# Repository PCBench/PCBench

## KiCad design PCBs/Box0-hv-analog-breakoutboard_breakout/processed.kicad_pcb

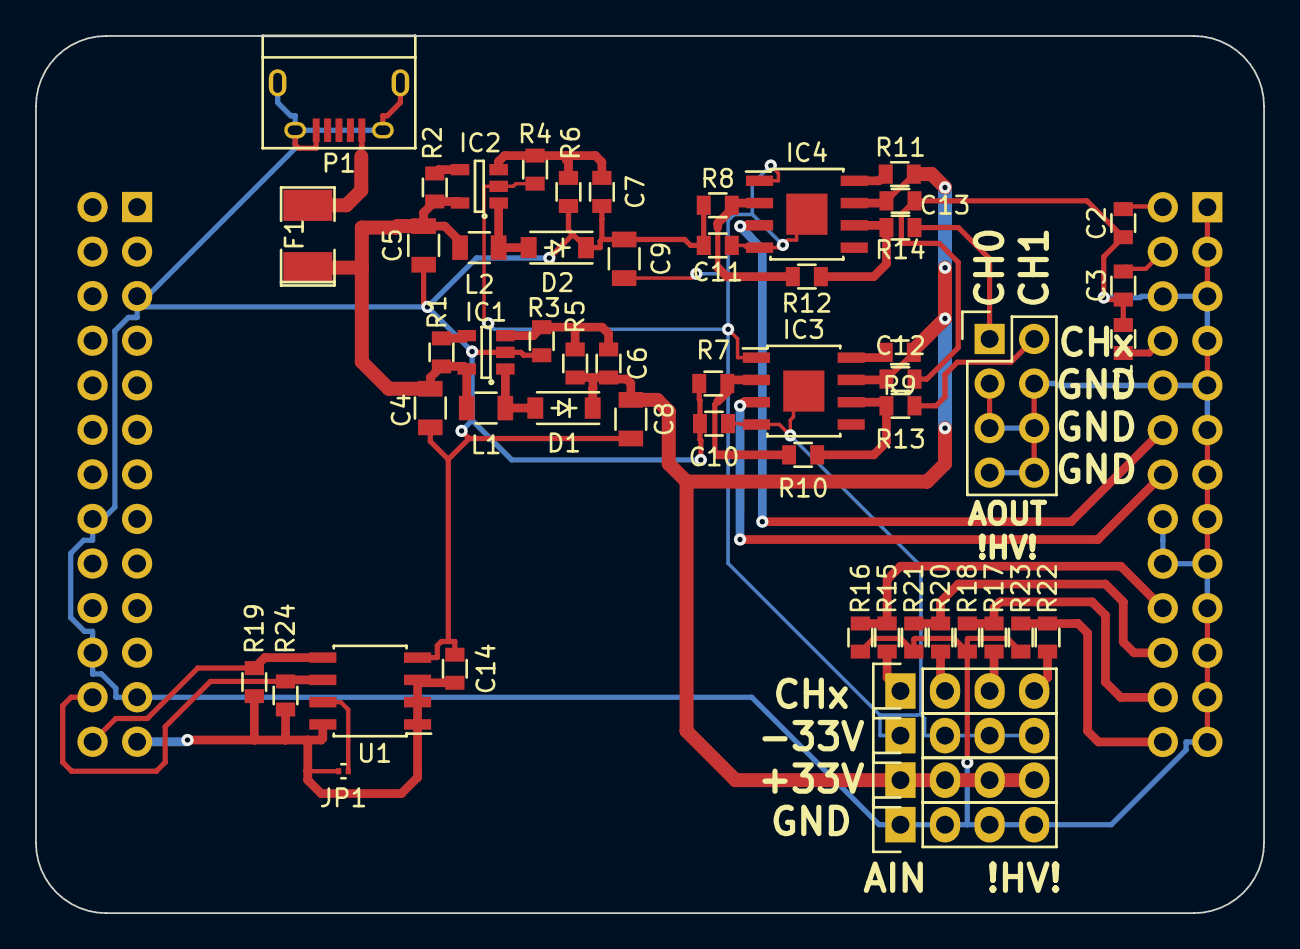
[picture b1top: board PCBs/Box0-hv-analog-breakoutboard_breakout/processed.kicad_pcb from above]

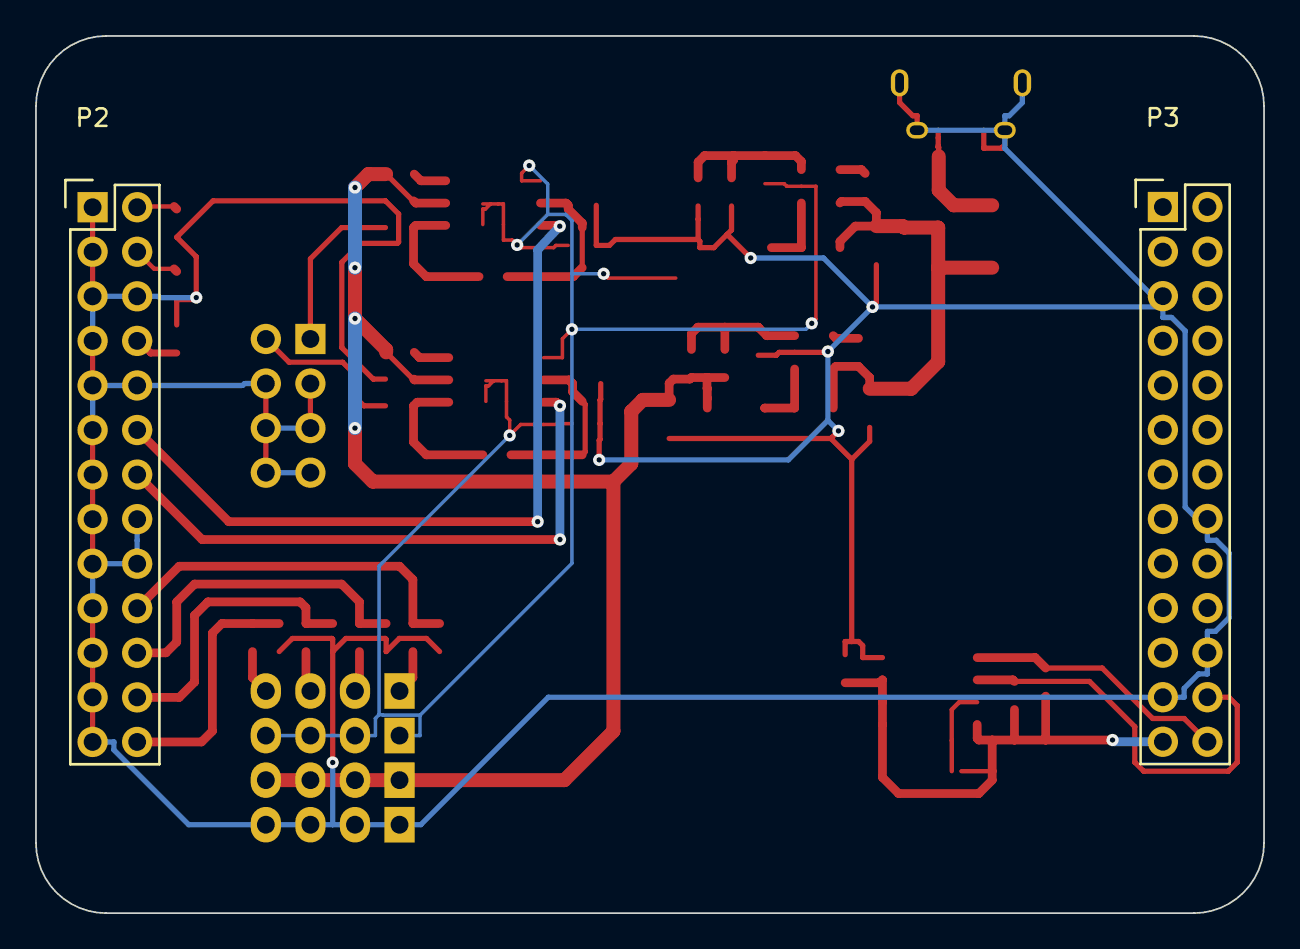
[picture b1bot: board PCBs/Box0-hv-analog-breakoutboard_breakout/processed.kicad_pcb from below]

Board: 2 copper layers, 70.0 x 50.0 mm, 57 parts (2 on the bottom side), 36 nets.

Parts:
C1, C2, C3: 100nF; 0603
C4, C5: 4.7u; 0805
C6, C7: 82p; 0603
C8, C9: 10u; 0805
C10, C11, C12, C13, C14: 100n; 0603
D1, D2: MBR0540; SOD-123
F1: F_Small; SMD-1210_Pol
IC1, IC2: LM2733; SOT-23-5
IC3, IC4: OPA454; SOIC-8-3.9*4.9mm_HP_to_P4
JP1: Jumper_NO_Small; C_0201
L1, L2: 10u; 0805
P1: USB_OTG; USB_Micro-B
P2: BASE_BOARD_ANALOG; Pin_Header_Straight_2x13
P3: BASE_BOARD_DIGITAL; Pin_Header_Straight_2x13
P4: CONN_02X04; Pin_Header_Straight_2x04
P5, P6, P7, P8: CONN_01X04; Pin_Header_Straight_1x04
R1, R2: 47K; 0603
R3, R4: 12K; 0603
R5, R6: 309K; 0603
R7, R8, R16, R18, R21, R23: 10K; 0603
R9, R11: 1M; 0603
R10, R12, R15, R17, R20, R22: 91K; 0603
R13, R14: 10R; 0603
R19, R24: 4.7K; 0603
U1: 24C16; SOIC-8_3.9x4.9mm_Pitch1.27mm

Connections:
5V: C4.1, C5.1, F1.1, IC1.5, IC2.5, L1.2, L2.2, R1.1, R2.1
+33V: C6.2, C8.1, C12.1, C13.1, D1.1, IC3.7, IC4.7, P6.1, P6.2, P6.3, P6.4, R5.2, R9.1, R11.1
-33V: C9.2, C10.1, C11.1, IC2.2, IC3.1, IC3.4, IC4.1, IC4.4, P7.1, P7.2, P7.3, P7.4, R4.2
/Box0 Interface/AIN0.0: P2.20, R15.1, R16.2
/Box0 Interface/AIN0.1: P2.22, R20.1, R21.2
/Box0 Interface/AIN0.2: P2.24, R17.1, R18.2
/Box0 Interface/AIN0.3: P2.26, R22.1, R23.2
/Box0 Interface/AOUT0.0: IC4.3, P2.12
/Box0 Interface/AOUT0.1: IC3.3, P2.14
/Box0 Interface/I2C0.SCL: P3.24, R24.2, U1.6
/Box0 Interface/I2C0.SDA: P3.26, R19.2, U1.5
ANALOG_NEG: C3.1, P2.4
ANALOG_POS: C2.1, P2.2
DIGITAL_EXT: C14.1, JP1.1, P3.25, R19.1, R24.1, U1.1, U1.2, U1.3, U1.8
GND: C1.2, C2.2, C3.2, C4.2, C5.2, C7.2, C8.2, C9.1, C10.2, C11.2, C12.2, C13.2, C14.2, D2.1, IC1.2, P1.5, P1.6, P2.1, P2.3, P2.5, P2.6, P2.7, P2.9, P2.10, P2.11, P2.13, P2.15, P2.16, P2.17, P2.18, P2.19, P2.21, P2.23, P2.25, P3.5, P3.16, P3.22, P3.23, P4.3, P4.4, P4.5, P4.6, P4.7, P4.8, P5.1, P5.2, P5.3, P5.4, R3.2, R6.2, R7.1, R8.1, R16.1, R18.1, R21.1, R23.1, U1.4
unnamed: C6.1, IC1.3, R3.1, R5.1
unnamed: C7.1, IC2.3, R4.1, R6.1
unnamed: D1.2, IC1.1, L1.1
unnamed: D2.2, IC2.1, L2.1
unnamed: F1.2, P1.1
unnamed: IC1.4, R1.2
unnamed: IC2.4, R2.2
unnamed: IC3.2, R7.2, R10.2
unnamed: IC3.6, R10.1, R13.2
unnamed: IC3.8, R9.2
unnamed: IC4.2, R8.2, R12.2
unnamed: IC4.6, R12.1, R14.2
unnamed: IC4.8, R11.2
unnamed: JP1.2, U1.7
unnamed: P4.1, R14.1
unnamed: P4.2, R13.1
unnamed: P8.1, R15.2
unnamed: P8.2, R20.2
unnamed: P8.3, R17.2
unnamed: P8.4, R22.2
VREF_EXT: C1.1, P2.8

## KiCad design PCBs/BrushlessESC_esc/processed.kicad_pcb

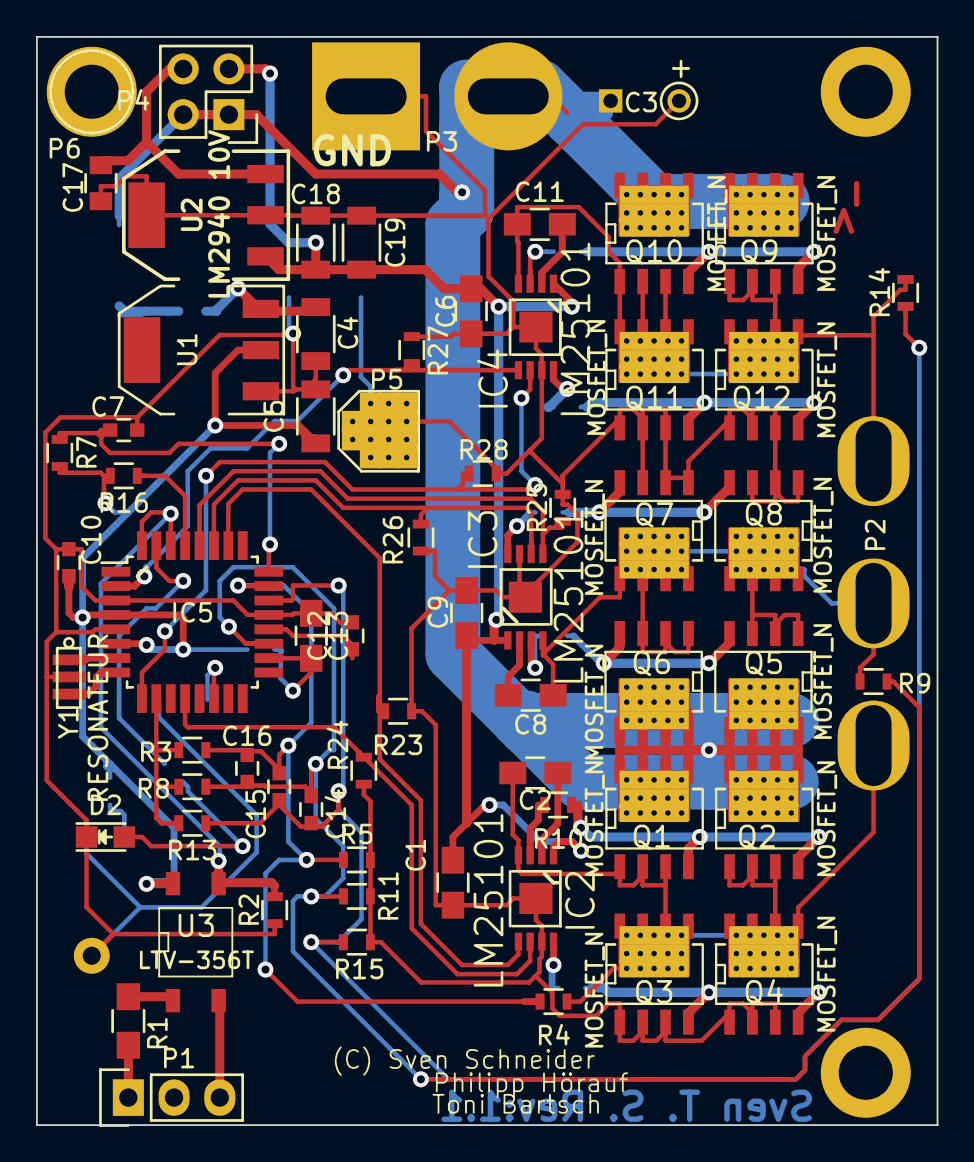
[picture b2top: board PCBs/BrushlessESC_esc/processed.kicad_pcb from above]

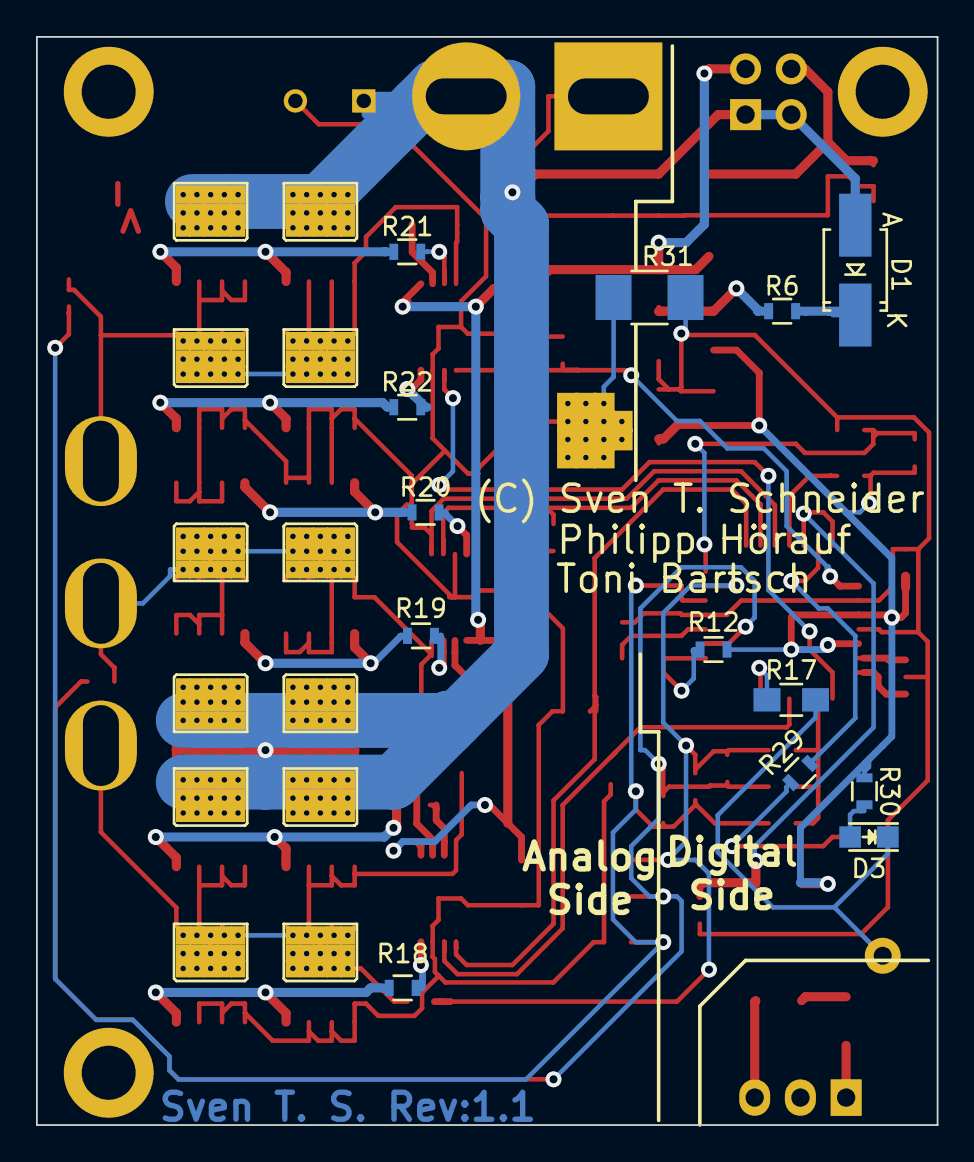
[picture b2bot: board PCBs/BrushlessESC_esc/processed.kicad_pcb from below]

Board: 2 copper layers, 50.0 x 60.5 mm, 79 parts (13 on the bottom side), 50 nets.

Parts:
C1, C2, C6, C8, C9, C11, C13: 1µ; C_0805_HandSoldering
C3: 220µ; C_Radial_D8_L13_P3.8
C4, C5, C18, C19: 10µ; C_1206
C7, C10, C12, C14, C15, C16: 100n; C_0603
C17: 470n; C_0805
D1: DIODE; SMA_Handsoldering
D2, D3: LED; LED-0805
IC2, IC3, IC4: LM25101; 8-MSOP
IC5: ATMEGA8-AI; TQFP-32_7x7mm_Pitch0.8mm
P1, P2: CONN_01X03; Socket_Strip_Straight_1x03
P3: CONN_01X02; Socket_Strip_Straight_1x02
P4: CONN_02X02; Socket_Strip_Straight_2x02
P5, P6: CONN_01X01; 1pin
Q1, Q2, Q3, Q4, Q5, Q6, Q7, Q8, Q9, Q10, Q11, Q12: MOSFET_N; SO8_WITH_Heatpipes_New
R1: R; R_0805_HandSoldering
R2: 10k; R_0603
R3, R5, R8, R11, R13, R15, R16: 3k3; R_0603
R4, R9, R14: 18k; R_0603
R6: 1; R_0603
R7: 1k5; R_0603
R10, R18, R19, R20, R21, R22: R; R_0603
R12, R29, R30: 100; R_0603
R17: 0 Bridge; R_0805_HandSoldering
R23, R24, R25, R26, R27, R28: PD; R_0603
R31: Bridge; R_1210_HandSoldering
U1: LD1117S50TR; SOT-223
U2: LM2940 10V; SOT223_GND_VO_VI
U3: LTV-356T; SO-4
Y1: RESONATEUR; CerOsc_3,2x1,3

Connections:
9V: C1.1, C6.1, C9.1, C18.1, C19.1, IC2.1, IC3.1, IC4.1, P4.2, U2.1
+5V: C5.1, C10.1, IC5.4, IC5.6, R7.2, R12.2, R16.2, R30.2, U1.2, U3.4
/A_Highside_Gate: Q1.G, Q2.G, R10.1
/A_Lowside_Gate: Q3.G, Q4.G, R18.1
/B_Highside_Gate: Q5.G, Q6.G, R19.1
/B_Lowside_Gate: Q7.G, Q8.G, R20.1
/C_Highside_Gate: Q9.G, Q10.G, R21.1
/C_Lowside_Gate: Q11.G, Q12.G, R22.1
/INPUT_GND: P1.3, U3.2
/INPUT_SIGNAL: P1.1, R1.2
/VBat_to_10V: C17.1, P4.4, U2.3
A: C2.2, IC2.4, P2.1, Q1.S, Q2.S, Q3.D, Q4.D, R4.1
A+: IC2.5, IC5.26, R23.2
A-: IC2.6, IC5.12, R24.2
B: C8.2, IC3.4, P2.2, Q5.S, Q6.S, Q7.D, Q8.D, R9.1
B+: IC3.5, IC5.28, R25.2
B-: IC3.6, IC5.27, R26.2
C: C11.2, IC4.4, P2.3, Q9.S, Q10.S, Q11.D, Q12.D, R14.1
C+: IC4.5, IC5.2, R27.2
C-: IC4.6, IC5.9, R28.2
D_GND: C4.2, C5.2, C7.2, C10.2, C12.2, C13.1, D2.1, D3.1, IC5.3, IC5.5, IC5.21, P6.1, R2.1, R17.2, R31.2, U1.1, Y1.2
GND: C1.2, C3.2, C6.2, C9.2, C17.2, C18.2, C19.2, IC2.7, IC2.PAD, IC3.7, IC3.PAD, IC4.7, IC4.PAD, P3.1, P5.1, Q3.S, Q4.S, Q7.S, Q8.S, Q11.S, Q12.S, R5.2, R11.2, R15.2, R23.1, R24.1, R25.1, R26.1, R27.1, R28.1, R31.1, U2.2
M: IC5.10, R3.2, R8.2, R13.2
unnamed: C2.1, IC2.2
unnamed: C4.1, R6.1, U1.3
unnamed: C8.1, IC3.2
unnamed: C11.1, IC4.2
unnamed: C12.1, IC5.20
unnamed: C13.2, IC5.18, R12.1
unnamed: D1.2, R6.2
unnamed: D2.2, R29.1
unnamed: D3.2, R30.1
unnamed: IC2.3, R10.2
unnamed: IC2.8, R18.2
unnamed: IC3.3, R19.2
unnamed: IC3.8, R20.2
unnamed: IC4.3, R21.2
unnamed: IC4.8, R22.2
unnamed: IC5.7, Y1.1
unnamed: IC5.8, Y1.3
unnamed: IC5.14, R17.1
unnamed: IC5.29, R16.1
unnamed: IC5.31, R29.2
unnamed: R1.1, U3.1
PWM: IC5.30, IC5.32, R2.2, U3.3
S_A: C15.1, C16.1, IC5.23, R3.1, R4.2, R5.1
S_B: C14.2, C16.2, IC5.19, R8.1, R9.2, R11.1
S_C: C14.1, C15.2, IC5.22, R13.1, R14.2, R15.1
S_PWR: C7.1, IC5.24, R7.1
V_BAT: C3.1, D1.1, P3.2, P4.1, P4.3, Q1.D, Q2.D, Q5.D, Q6.D, Q9.D, Q10.D

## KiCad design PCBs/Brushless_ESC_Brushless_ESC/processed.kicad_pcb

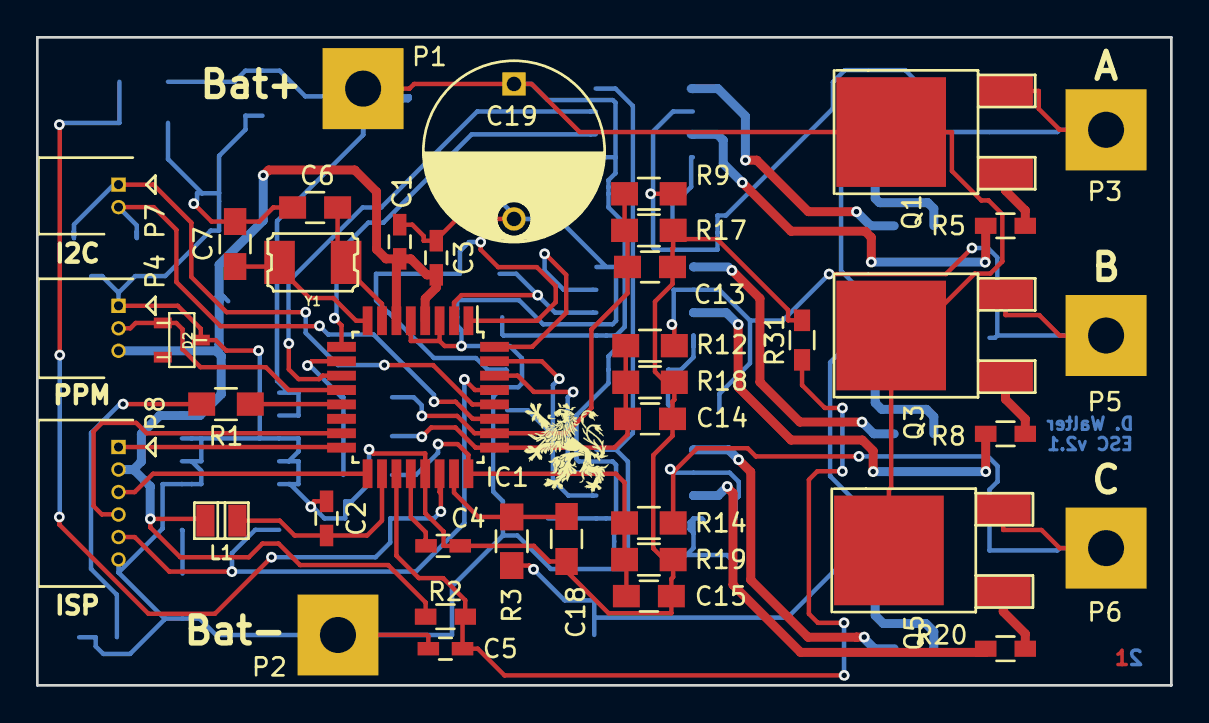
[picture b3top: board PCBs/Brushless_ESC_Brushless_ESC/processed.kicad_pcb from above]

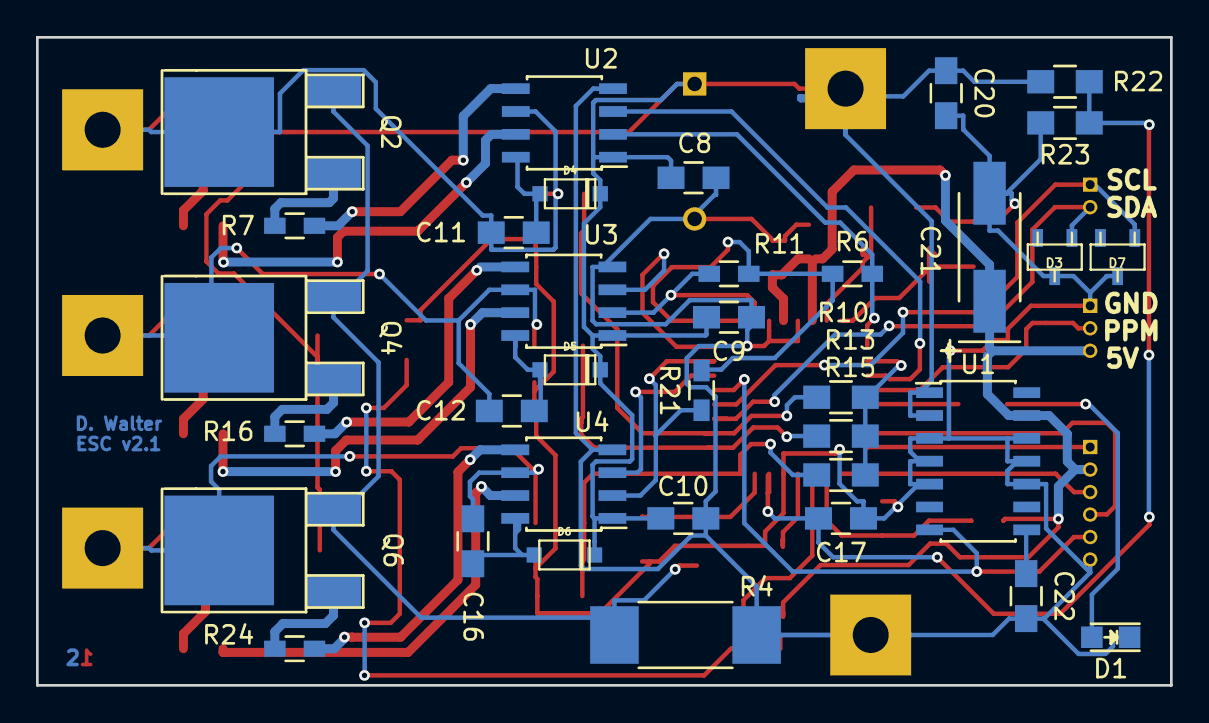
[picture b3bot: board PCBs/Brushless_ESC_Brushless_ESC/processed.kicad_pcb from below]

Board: 2 copper layers, 63.0 x 36.0 mm, 76 parts (35 on the bottom side), 50 nets.

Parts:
C1, C2, C3, C4, C5: 100nF; C_0603_HandSoldering
C6, C7: 8pF; C_0805_HandSoldering
C8, C9, C10, C13, C14, C15, C17, C18, C22: 100nF; C_0805_HandSoldering
C11, C12, C16: 220nF; C_0805_HandSoldering
C19: 1000µF; C_Radial_D10_L20_P7.5
C20: 470nF; C_0805_HandSoldering
C21: 22µF; TantalC_SizeC_EIA-6032_HandSoldering
D1: LED; LED_0805
D2, D3, D7: ZD5,6; sot23
D4, D5, D6: BAS21; sod123
IC1: ATMEGA88PA-A; TQFP-32_7x7mm_Pitch0.8mm
L1: 10µH; inductor_smd_0805
P1: Battery+; SolderWirePad_single_2mmDrill
P2, P2_2: Battery-; SolderWirePad_single_2mmDrill
P3: Coil_A; SolderWirePad_single_2mmDrill
P4: PPM; Molex_PicoBlade_53048-0310
P5: Coil_B; SolderWirePad_single_2mmDrill
P6: Coil_C; SolderWirePad_single_2mmDrill
P7: I2C; Molex_PicoBlade_53048-0210
P8: ISP; Molex_PicoBlade_53048-0610
Q1, Q2, Q3, Q4, Q5, Q6: IRL7843; TO-252-2Lead
R1: 220R; R_0805_HandSoldering
R2: 1k5; R_0603_HandSoldering
R3: 680R; R_0805_HandSoldering
R4: 0R02/5W; R_2512_HandSoldering
R5, R7, R8, R16, R20, R24: 47R; R_0603_HandSoldering
R6, R11, R21: 1k; R_0603_HandSoldering
R9, R10, R12, R13, R14, R15, R17, R18, R19: 4k7; R_0805_HandSoldering
R22: 1k5; R_0805_HandSoldering
R23: 470R; R_0805_HandSoldering
R31: 470R; R_0603_HandSoldering
U1: TLE4267; SOIC-14_3.9x8.7mm_Pitch1.27mm
U2, U3, U4: IR2104; SOIC-8_3.9x4.9mm_Pitch1.27mm
Y1: 20Mhz; crystal_smd_5x3.2mm

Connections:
+5V: C1.1, C3.1, C21.1, IC1.4, IC1.6, L1.2, P4.3, P8.2, R2.2, U1.13
+BATT: C8.1, C9.1, C10.1, C19.1, C20.1, D4.2, D5.2, D6.2, P1.1, Q1.2, Q3.2, Q5.2, R22.2, U1.1, U1.2, U2.1, U3.1, U4.1
/Controller//SD_A: IC1.11, U2.3
/Controller//SD_B: IC1.32, U3.3
/Controller//SD_C: IC1.30, U4.3
/Controller/BEMF_A: C13.1, IC1.26, R9.1, R10.2, R17.2
/Controller/BEMF_B: C14.1, IC1.25, R12.1, R13.2, R18.2
/Controller/BEMF_C: C15.1, IC1.24, R14.1, R15.2, R19.2
/Controller/BEMF_Center: IC1.10, R10.1, R13.1, R15.1
/Controller/BatCurrent+: C18.1, IC1.23, R3.2
/Controller/IN_A: IC1.9, R6.1, U2.2
/Controller/IN_B: IC1.2, R11.1, U3.2
/Controller/IN_C: IC1.31, R21.1, U4.2
/Controller/PPM: D2.1, IC1.12, P4.2
/Controller/PWM: IC1.1, R6.2, R11.2, R21.2
/Controller/Reset: IC1.29, P8.5, U1.7
/Controller/SCL: D7.1, IC1.28, P7.1
/Controller/SDA: D3.1, IC1.27, P7.2
/Controller/T_Sense: C5.1, IC1.19, R2.1, R31.2
/Controller/V_Bat: C17.1, IC1.22, R22.1, R23.2
/Power/Coil_A: C11.2, P3.1, Q1.3, Q2.2, R9.2, U2.6
/Power/Coil_B: C12.2, P5.1, Q3.3, Q4.2, R12.2, U3.6
/Power/Coil_C: C16.2, P6.1, Q5.3, Q6.2, R14.2, U4.6
GND: C1.2, C2.2, C3.2, C4.2, C5.2, C6.2, C7.1, C8.2, C9.2, C10.2, C13.2, C14.2, C15.2, C17.2, C18.2, C19.2, C20.2, C21.2, C22.2, D1.1, D2.2, D3.2, D7.2, IC1.3, IC1.5, IC1.21, P2.1, P4.1, P8.6, R4.1, R17.1, R18.1, R19.1, R23.1, R31.1, U1.3, U1.4, U1.5, U1.10, U1.11, U1.12, U2.4, U3.4, U4.4
unnamed: C2.1, IC1.18, L1.1
unnamed: C4.1, IC1.20
unnamed: C6.1, IC1.7, Y1.1
unnamed: C7.2, IC1.8, Y1.2
unnamed: C11.1, D4.1, U2.8
unnamed: C12.1, D5.1, U3.8
unnamed: C16.1, D6.1, U4.8
unnamed: C22.1, U1.8
unnamed: D1.2, R1.1
unnamed: IC1.13, R1.2
unnamed: IC1.15, P8.4
unnamed: IC1.16, P8.1
unnamed: IC1.17, P8.3
unnamed: Q1.1, R5.1
unnamed: Q2.1, R7.1
unnamed: Q2.3, Q4.3, Q6.3, R3.1, R4.2
unnamed: Q3.1, R8.1
unnamed: Q4.1, R16.1
unnamed: Q5.1, R20.1
unnamed: Q6.1, R24.1
unnamed: R5.2, U2.7
unnamed: R7.2, U2.5
unnamed: R8.2, U3.7
unnamed: R16.2, U3.5
unnamed: R20.2, U4.7
unnamed: R24.2, U4.5

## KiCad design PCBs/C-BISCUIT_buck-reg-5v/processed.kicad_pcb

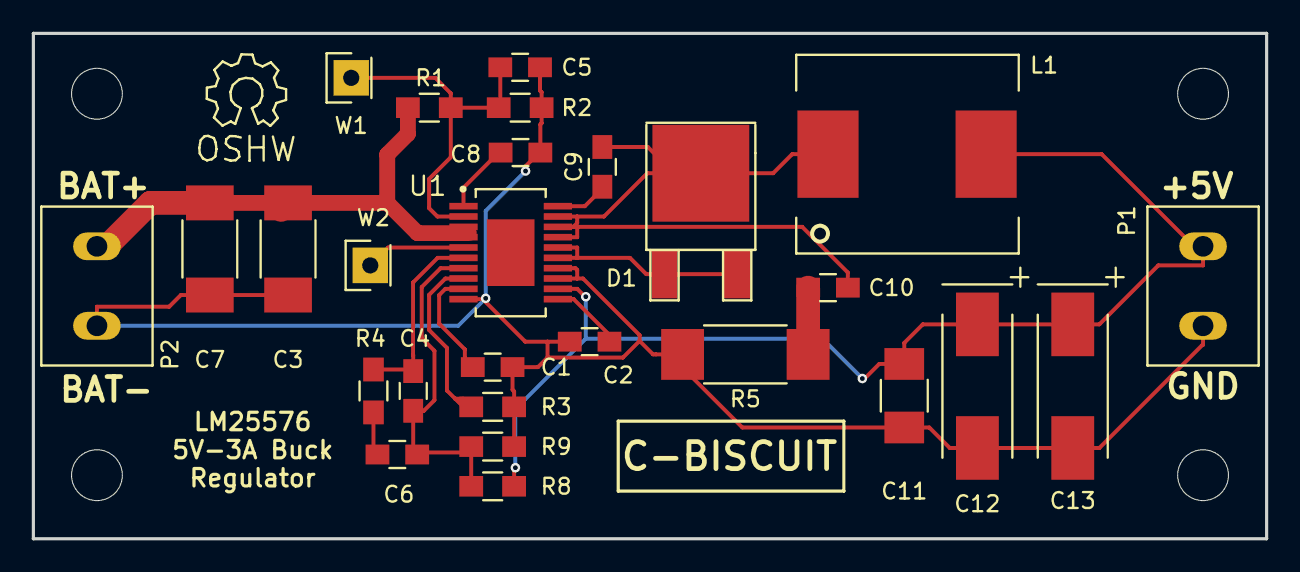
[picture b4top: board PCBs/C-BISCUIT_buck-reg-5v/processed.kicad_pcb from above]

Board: 2 copper layers, 77.6 x 31.8 mm, 27 parts (0 on the bottom side), 16 nets.

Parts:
C1, C10: 330pF; C_0805_HandSoldering
C2, C6: 0.01uF; C_0805_HandSoldering
C3, C7: 2.2uF; C_1812_HandSoldering
C4, C5: DNP; C_0805_HandSoldering
C8: 0.47uF; C_0805_HandSoldering
C9: 0.022uF; C_0805_HandSoldering
C11: 22uF; C_1210_HandSoldering
C12, C13: 150uF; TantalC_SizeD_EIA-7343_HandSoldering
D1: CSHD6-60C; TO-252-2Lead
L1: 33uH; Inductor_EB_DR127
P1, P2: CONN_01X02; Conn_01x02_5.0mm_Phoenix_1935161
R1, R2: DNP; R_0805_HandSoldering
R3: 20.5K; R_0805_HandSoldering
R4: 49.9K; R_0805_HandSoldering
R5: 10; R_2512_HandSoldering
R8: 15.4K; R_0805_HandSoldering
R9: 4.99K; R_0805_HandSoldering
U1: LM25576; SOIC-20-1EP
W1, W2: TP; Socket_Strip_Straight_1x01

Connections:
+5V: C11.1, C12.1, C13.1, L1.2, P1.1, R8.1, U1.12
/BAT_IN: C3.1, C7.1, P2.1, R1.1, U1.3, U1.4
/BST: C9.2, U1.20
/COMP: C4.1, R4.1, U1.6
/FB: C4.2, C6.2, R8.2, R9.1, U1.7
/IS: D1.1, D1.3, U1.15, U1.16
/RAMP: C1.2, U1.9
/RT: R3.1, U1.8
/SD: C5.1, R1.2, R2.1, U1.2, W1.1
/SS: C2.1, U1.11
/SW: C9.1, C10.2, D1.2, L1.1, U1.17, U1.18, U1.19
/SYNC: U1.5, W2.1
/VCC: C8.1, U1.1
GND: C1.1, C2.2, C3.2, C5.2, C7.2, C8.2, C11.2, C12.2, C13.2, P1.2, P2.2, R2.2, R3.2, R5.2, R9.2, U1.10, U1.13, U1.14
unnamed: C6.1, R4.2
unnamed: C10.1, R5.1

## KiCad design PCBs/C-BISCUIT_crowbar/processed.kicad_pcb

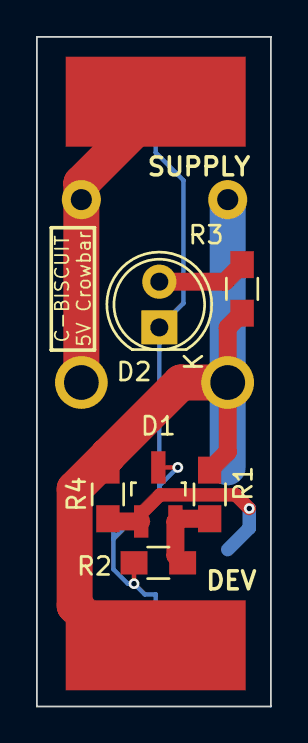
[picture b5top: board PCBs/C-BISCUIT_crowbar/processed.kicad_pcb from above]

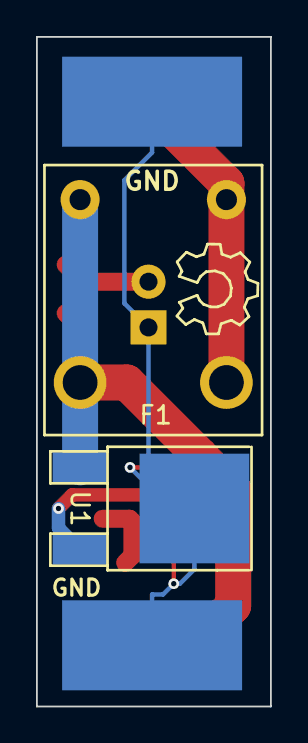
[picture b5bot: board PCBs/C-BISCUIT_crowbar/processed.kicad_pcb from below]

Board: 2 copper layers, 13.0 x 37.2 mm, 12 parts (4 on the bottom side), 6 nets.

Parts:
D1: LM431; SOT-23_Handsoldering
D2: RED; LED-5MM
F1: 3A; 3549-BLADE-CLIP
P1, P2, P3, P4: CONN_01X01; SolderWirePad_single_SMD_5x10mm
R1: 3.48K; R_0805_HandSoldering
R2: 2.49K; R_0805_HandSoldering
R3: 200; R_0805_HandSoldering
R4: 220; R_0805_HandSoldering
U1: BT137S; TO-252-2Lead

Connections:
/DEVICE: F1.2, P2.1, R1.1, R3.1, R4.1, U1.1
/SUPPLY: F1.1, P1.1
GND: D1.3, D2.1, P3.1, P4.1, R2.1, U1.2
unnamed: D1.1, R4.2, U1.3
unnamed: D1.2, R1.2, R2.2
unnamed: D2.2, R3.2

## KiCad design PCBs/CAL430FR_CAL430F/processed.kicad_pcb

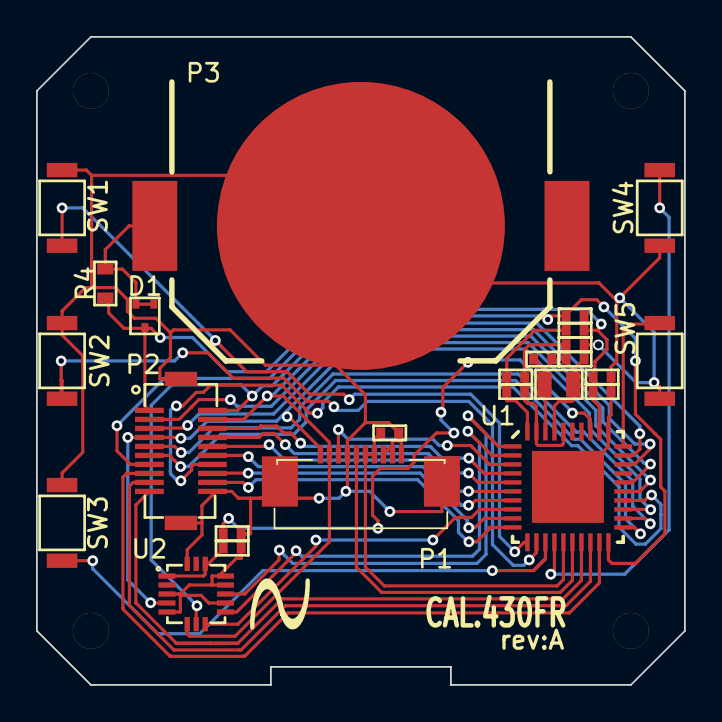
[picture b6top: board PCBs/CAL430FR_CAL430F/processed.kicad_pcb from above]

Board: 2 copper layers, 36.0 x 36.0 mm, 29 parts (0 on the bottom side), 37 nets.

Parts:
C1, C2, C6: 0.1u; C1005
C3, C4: 10p; C1005
C5, C8, C9: 1u; C1005
C7: C; C1005
D1: BAS70T-05T-7-F; SOT-523
Drill_M2, Drill_M2_2, Drill_M2_3, Drill_M2_4: VAL**; Drill_M2
P1: 57246-1071; 52746-1071
P2: DF12#-20DP(86); DF12_20_metal
P3: BAT_HLD_001; HLD-001
R1: 47k; R1005
R2, R3: 0; R1005
R4: 0; R1608
SW1, SW2, SW3, SW4, SW5: SW_PUSH; B3U-3000P
U1: MSP430FR5949IR; QFN40
U2: ADXL362; LGA16_ADXL
X1: 32.768 6pF; CRYSTAL_2012

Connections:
+3.3V: C2.1, C5.1, D1.3, P2.1, R1.2, R2.1, R4.2, U1.32
ADXL_PWR: C1.1, C9.1, U1.33, U2.1, U2.14
CS1: P1.3, U1.3
CS2: U1.8, U2.8
DISP: P1.5, U1.16
GND: C1.2, C2.2, C5.2, C7.2, C9.2, P1.4, P1.8, P1.9, P1.10, P1.11, P1.12, P2.20, P2.21, P2.22, P3.1, R3.1, SW1.2, SW2.2, SW3.2, SW4.2, SW5.2, U1.31, U1.41, U2.3, U2.5, U2.10, U2.12, U2.13, U2.16
INT_A1: U1.1, U2.11
INT_A2: U1.2, U2.9
LCD_Power: C7.1, P1.6, P1.7, U1.15
MISO: P2.2, U1.29, U2.7
MOSI: P1.2, P2.4, U1.28, U2.6
unnamed: C3.1, U1.38, X1.2
unnamed: C3.2, C4.2, C6.2, C8.2, R3.2, U1.36, U1.39
unnamed: C4.1, U1.37, X1.1
unnamed: C6.1, C8.1, R2.2, U1.40
unnamed: D1.1, D1.2, P3.2, R4.1
P1.4: P2.16, U1.9
P1.5: P2.18, U1.10
P3.0: P2.6, U1.4
P3.1: P2.8, U1.5
P3.2: P2.10, U1.6
P3.3: P2.12, U1.7
P3.4: P2.14, U1.24
P3.5: P2.5, U1.25
P3.6: P2.3, U1.26
P4.4: SW5.1, U1.30
PJ.0: SW1.1, U1.11
PJ.1: SW2.1, U1.12
PJ.2: SW3.1, U1.13
PJ.3: SW4.1, U1.14
RST: P2.13, R1.1, U1.20
RXD0: P2.9, U1.22
RXD1: P2.17, U1.18
SCLK: P1.1, P2.7, U1.23, U2.4
TST: P2.15, U1.19
TXD0: P2.11, U1.21
TXD1: P2.19, U1.17

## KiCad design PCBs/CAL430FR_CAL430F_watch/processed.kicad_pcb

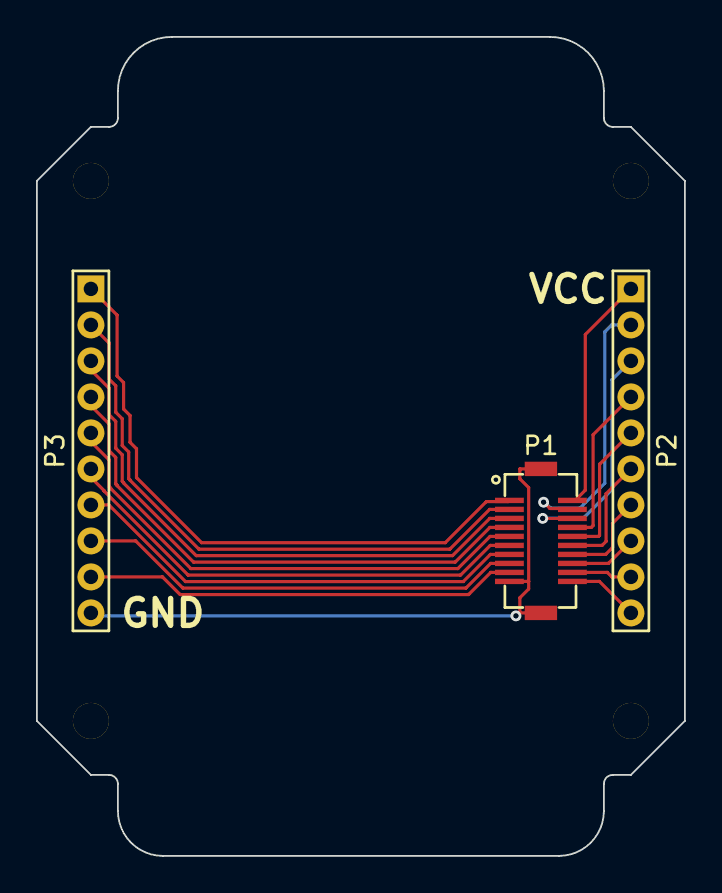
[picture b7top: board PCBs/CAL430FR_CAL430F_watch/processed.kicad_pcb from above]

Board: 2 copper layers, 36.0 x 45.5 mm, 7 parts (0 on the bottom side), 20 nets.

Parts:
Drill_M2, Drill_M2_2, Drill_M2_3, Drill_M2_4: VAL**; Drill_M2
P1: DF12#-20DP(86); DF12_20(B)_metal
P2, P3: CONN_10; P1-10_2mm

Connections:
+3.3V: P1.1, P2.1
GND: P1.20, P1.21, P1.22, P3.10
unnamed: P1.2, P3.1
unnamed: P1.3, P2.2
unnamed: P1.4, P3.2
unnamed: P1.5, P2.3
unnamed: P1.6, P3.3
unnamed: P1.7, P2.4
unnamed: P1.8, P3.4
unnamed: P1.9, P2.5
unnamed: P1.10, P3.5
unnamed: P1.11, P2.6
unnamed: P1.12, P3.6
unnamed: P1.13, P2.7
unnamed: P1.14, P3.7
unnamed: P1.15, P2.8
unnamed: P1.16, P3.8
unnamed: P1.17, P2.9
unnamed: P1.18, P3.9
unnamed: P1.19, P2.10
